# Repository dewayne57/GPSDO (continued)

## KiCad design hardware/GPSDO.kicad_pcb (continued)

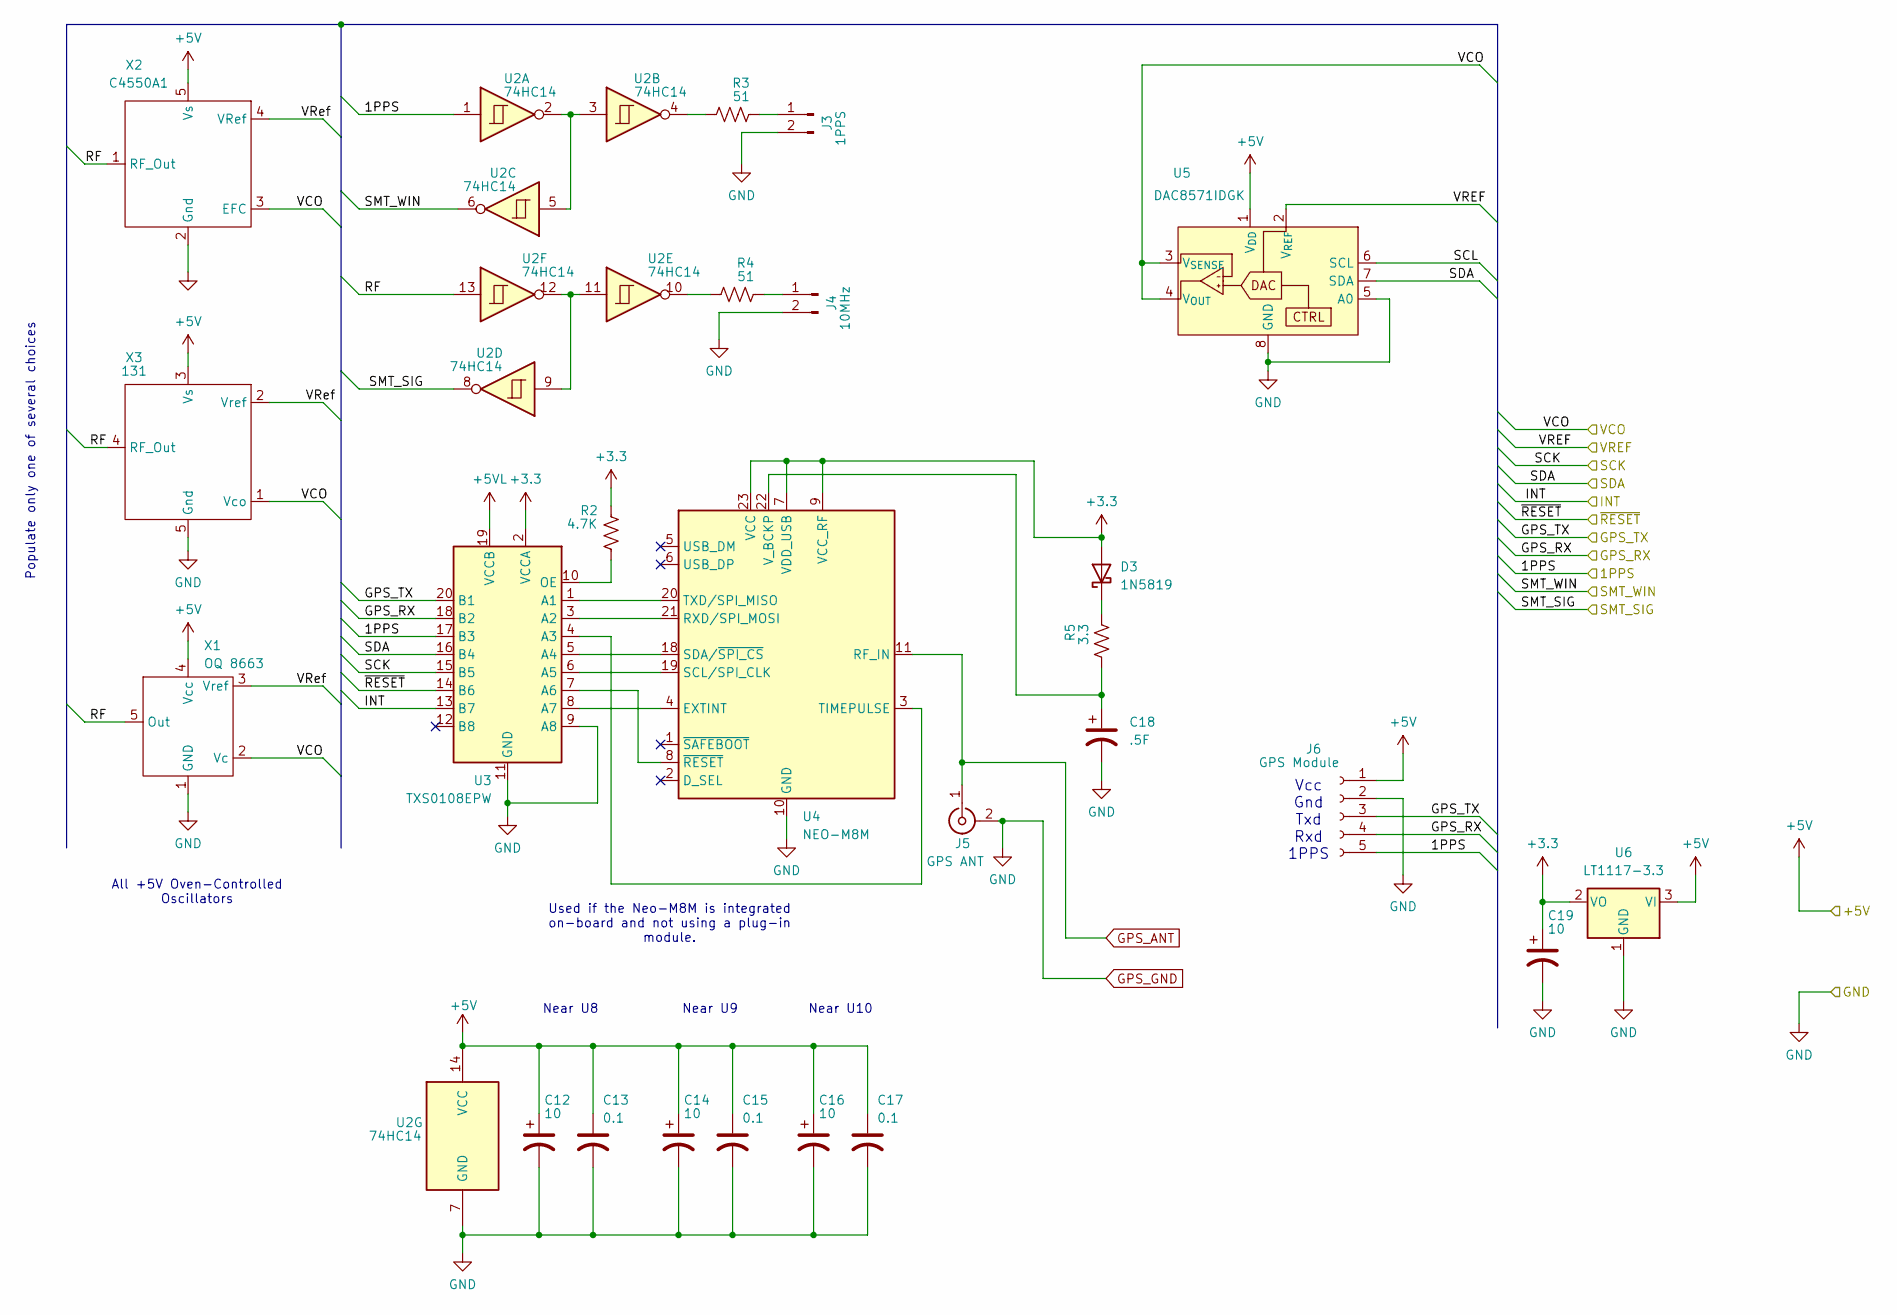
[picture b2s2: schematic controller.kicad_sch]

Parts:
C12, C14, C16, C19: 10; CP_Elec_5x5.4
C13, C15, C17: 0.1; C_0805_2012Metric_Pad1.18x1.45mm_HandSolder
C18: .5F
D3: 1N5819; D_DO-41_SOD81_P10.16mm_Horizontal
J3: 1PPS; PinHeader_1x02_P2.54mm_Vertical
J4: 10MHz; PinHeader_1x02_P2.54mm_Vertical
J5: GPS ANT; SMA_Amphenol_901-144_Vertical
J6: GPS Module; PinHeader_1x05_P2.54mm_Vertical
R2: 4.7K; R_0805_2012Metric_Pad1.20x1.40mm_HandSolder
R3, R4: 51; R_0805_2012Metric_Pad1.20x1.40mm_HandSolder
R5: 3.3; R_0805_2012Metric_Pad1.20x1.40mm_HandSolder
U2: 74HC14; SO-14_5.3x10.2mm_P1.27mm
U3: TXS0108EPW; TSSOP-20_4.4x6.5mm_P0.65mm
U4: NEO-M8M; ublox_NEO
U5: DAC8571IDGK; MSOP-8_3x3mm_P0.65mm
U6: LT1117-3.3; SOT-223
X1: OQ 8663; OQ8663
X2: C4550A1; C4550-OCXO
X3: 131; ISOTEMP 131

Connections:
+3.3: C19.1, D3.2 (A), R2.1, U3.2 (VCCA), U4.7 (VDD_USB), U4.9 (VCC_RF), U4.23 (VCC), U6.2 (VO); also elsewhere on the board
+5V: C12.1, C13.1, C14.1, C15.1, C16.1, C17.1, J6.1, U2.14 (VCC), U5.1 (V_{DD}), U6.3 (VI), X1.4 (Vcc), X2.5 (Vs), X3.3 (Vs); also elsewhere on the board
+5VL: U3.19 (VCCB)
/Loop Controller/1PPS: J6.5, U2.1, U3.17 (B3); also elsewhere on the board
/Loop Controller/GPS_RX: J6.4, U3.18 (B2); also elsewhere on the board
/Loop Controller/GPS_TX: J6.3, U3.20 (B1); also elsewhere on the board
/Loop Controller/INT: U3.13 (B7); also elsewhere on the board
/Loop Controller/RF: U2.13, X1.5 (Out), X2.1 (RF_Out), X3.4 (RF_Out)
/Loop Controller/SCK: U3.15 (B5)
/Loop Controller/SCL: U5.6 (SCL)
/Loop Controller/SDA: U3.16 (B4), U5.7 (SDA); also elsewhere on the board
/Loop Controller/SMT_SIG: U2.8; also elsewhere on the board
/Loop Controller/SMT_WIN: U2.6; also elsewhere on the board
/Loop Controller/VCO: U5.3 (V_{SENSE}), U5.4 (V_{OUT}), X1.2 (Vc), X2.3 (EFC), X3.1 (Vco); also elsewhere on the board
/Loop Controller/VREF: U5.2 (V_{REF}); also elsewhere on the board
/Loop Controller/VRef: X1.3 (Vref), X2.4 (VRef), X3.2 (Vref)
/Loop Controller/~RESET: U3.14 (B6); also elsewhere on the board
Earth_Protective: C12.2, C13.2, C14.2, C15.2, C16.2, C17.2, C18.2, C19.2, J3.2, J4.2, J5.2 (Ext), J6.2, U2.7 (GND), U3.9 (A8), U3.11 (GND), U4.10 (GND), U4.12 (GND), U4.13 (GND), U4.24 (GND), U5.5 (A0), U5.8 (GND), U6.1 (GND), X1.1 (GND), X2.2 (Gnd), X3.5 (Gnd); also elsewhere on the board
GPS_ANT: J5.1 (In), U4.11 (RF_IN)
unnamed: D3.1 (K), R5.2
unnamed: J3.1, R3.2
unnamed: J4.1, R4.2
unnamed: R3.1, U2.4
unnamed: R4.1, U2.10
unnamed: U2.2, U2.3, U2.5
unnamed: U2.9, U2.11, U2.12
unnamed: U3.1 (A1), U4.20 (TXD/SPI_MISO)
unnamed: U3.3 (A2), U4.21 (RXD/SPI_MOSI)
unnamed: U3.4 (A3), U4.3 (TIMEPULSE)
unnamed: U3.5 (A4), U4.18 (SDA/~SPI_CS)
unnamed: U3.6 (A5), U4.19 (SCL/SPI_CLK)
unnamed: U3.7 (A6), U4.8 (~RESET)
unnamed: U3.8 (A7), U4.4 (EXTINT)
unnamed: R2.2, U3.10 (OE)
unnamed: C18.1, R5.1, U4.22 (V_BCKP)

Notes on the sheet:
Near U8
Vcc Gnd Txd Rxd 1PPS
Near U10
Used if the Neo-M8M is integrated on-board and not using a plug-in module.
Populate only one of several choices
Near U9
All +5V Oven-Controlled Oscillators

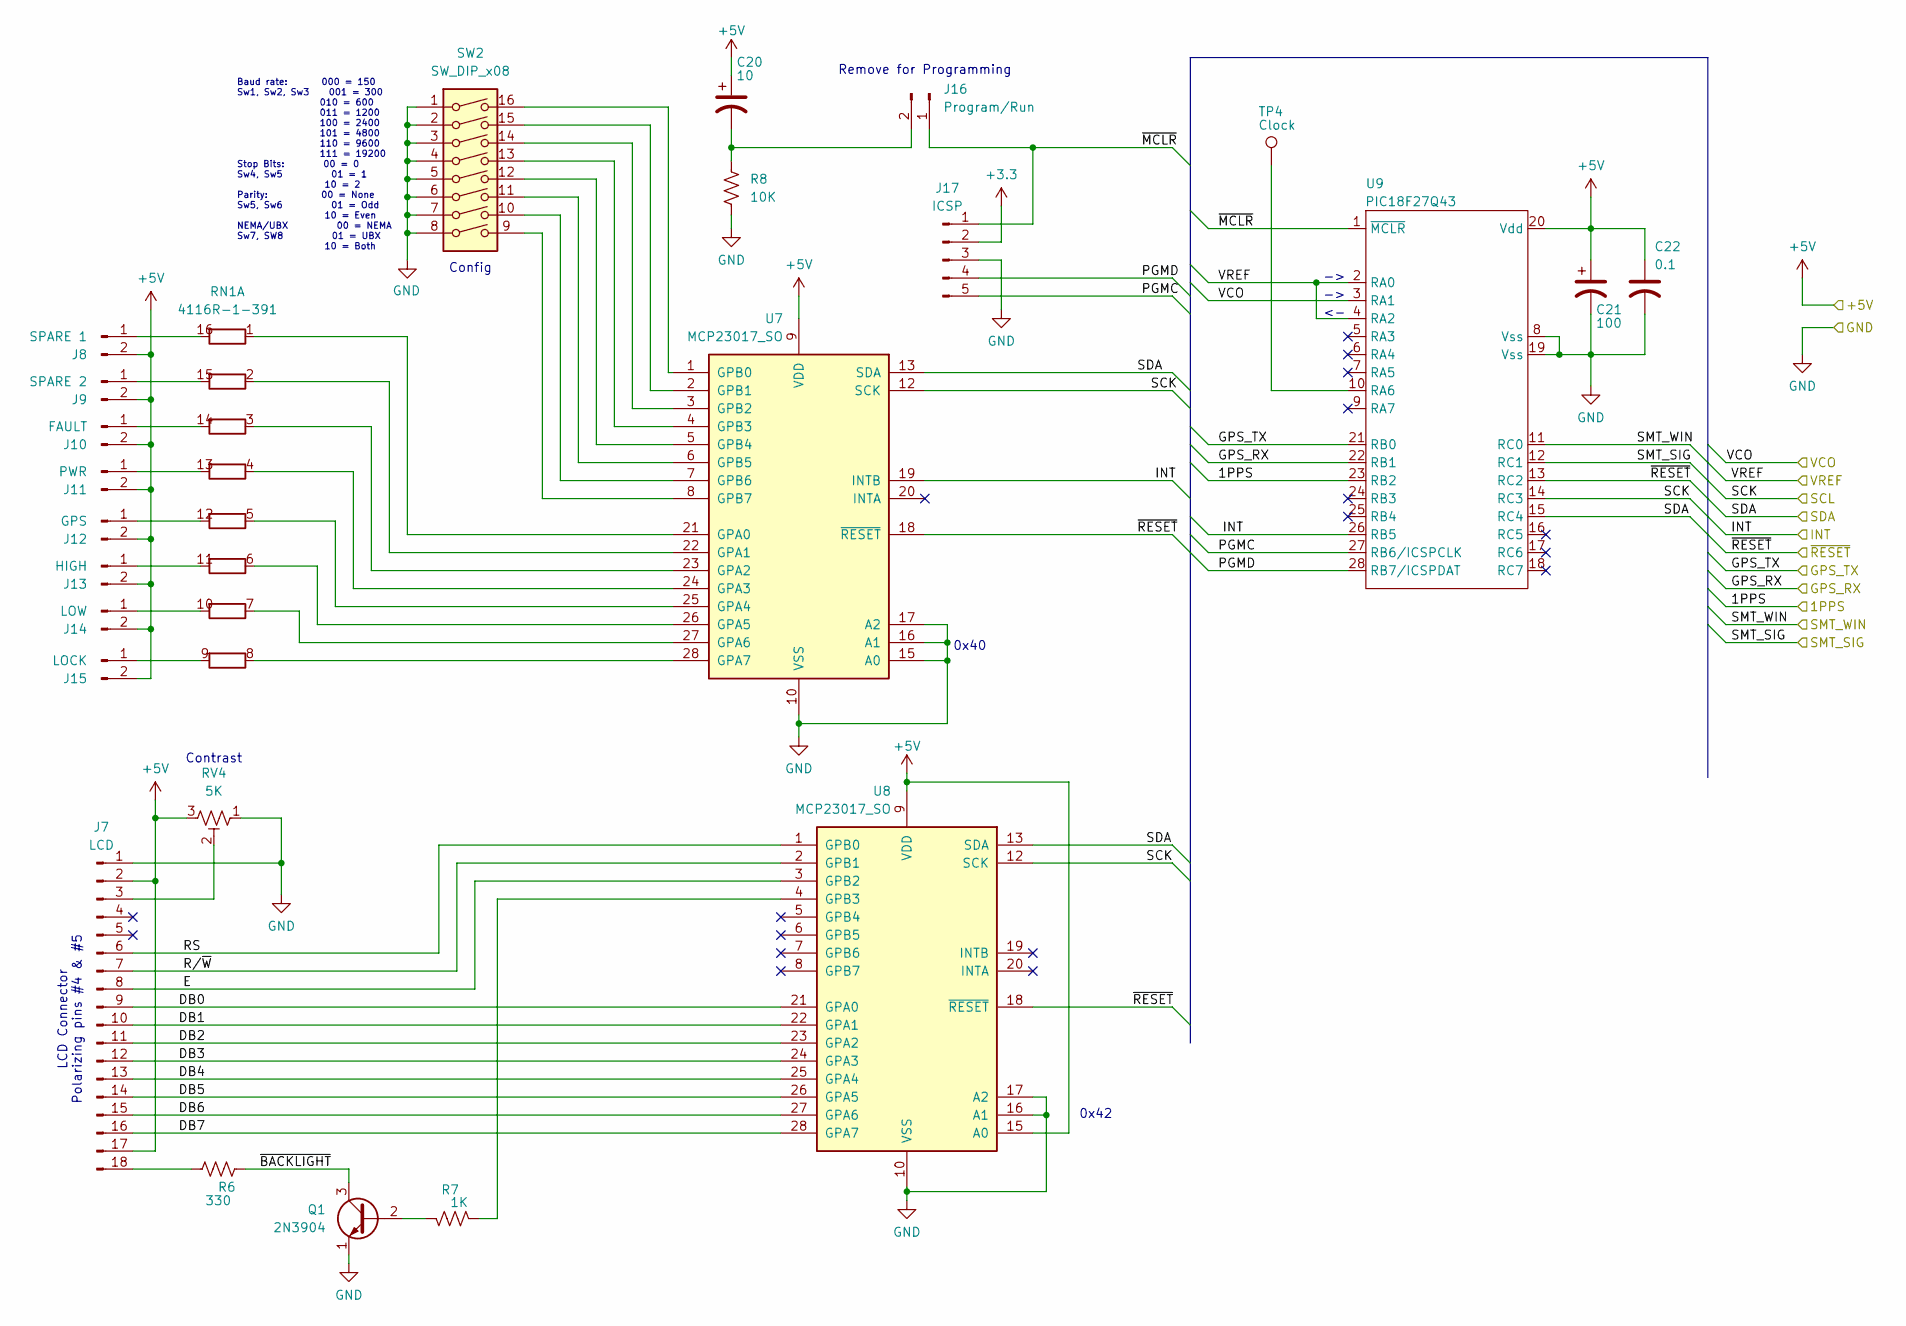
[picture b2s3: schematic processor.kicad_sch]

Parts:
C20: 10; CP_Elec_5x5.4
C21: 100; CP_Elec_6.3x7.7
C22: 0.1; C_0805_2012Metric_Pad1.18x1.45mm_HandSolder
J7: LCD; PinHeader_1x18_P2.54mm_Vertical
J8: SPARE 1; PinHeader_1x02_P2.54mm_Vertical
J9: SPARE 2; PinHeader_1x02_P2.54mm_Vertical
J10: FAULT; PinHeader_1x02_P2.54mm_Vertical
J11: PWR; PinHeader_1x02_P2.54mm_Vertical
J12: GPS; PinHeader_1x02_P2.54mm_Vertical
J13: HIGH; PinHeader_1x02_P2.54mm_Vertical
J14: LOW; PinHeader_1x02_P2.54mm_Vertical
J15: LOCK; PinHeader_1x02_P2.54mm_Vertical
J16: Program/Run; PinHeader_1x02_P2.54mm_Vertical
J17: ICSP; PinHeader_1x05_P2.54mm_Vertical
Q1: 2N3904; TO-92_Inline
R6: 330; R_0805_2012Metric_Pad1.20x1.40mm_HandSolder
R7: 1K; R_0805_2012Metric_Pad1.20x1.40mm_HandSolder
R8: 10K; R_0805_2012Metric_Pad1.20x1.40mm_HandSolder
RN1: 4116R-1-391; DIP-16_W7.62mm_LongPads
RV4: 5K; Potentiometer_Bourns_3296W_Vertical
SW2: SW_DIP_x08; DIP-16_W7.62mm_LongPads
TP4: Clock
U7, U8: MCP23017_SO; SOIC-28W_7.5x17.9mm_P1.27mm
U9: PIC18F27Q43; SOIC-28W_7.5x17.9mm_P1.27mm

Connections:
+3.3: J17.2; also elsewhere on the board
+5V: C20.1, C21.1, C22.1, J7.2, J7.17, J8.2, J9.2, J10.2, J11.2, J12.2, J13.2, J14.2, J15.2, RV4.3, U7.9 (VDD), U8.9 (VDD), U8.15 (A0), U9.20 (Vdd); also elsewhere on the board
/Loop Controller/1PPS: U9.23 (RB2); also elsewhere on the board
/Loop Controller/GPS_RX: U9.22 (RB1); also elsewhere on the board
/Loop Controller/GPS_TX: U9.21 (RB0); also elsewhere on the board
/Loop Controller/INT: U7.19 (INTB), U9.26 (RB5); also elsewhere on the board
/Loop Controller/SDA: U7.13 (SDA), U8.13 (SDA), U9.15 (RC4); also elsewhere on the board
/Loop Controller/SMT_SIG: U9.12 (RC1); also elsewhere on the board
/Loop Controller/SMT_WIN: U9.11 (RC0); also elsewhere on the board
/Loop Controller/VCO: U9.3 (RA1); also elsewhere on the board
/Loop Controller/VREF: U9.2 (RA0), U9.4 (RA2); also elsewhere on the board
/Loop Controller/~RESET: U7.18 (~RESET), U8.18 (~RESET), U9.13 (RC2); also elsewhere on the board
/Processor/DB0: J7.9, U8.21 (GPA0)
/Processor/DB1: J7.10, U8.22 (GPA1)
/Processor/DB2: J7.11, U8.23 (GPA2)
/Processor/DB3: J7.12, U8.24 (GPA3)
/Processor/DB4: J7.13, U8.25 (GPA4)
/Processor/DB5: J7.14, U8.26 (GPA5)
/Processor/DB6: J7.15, U8.27 (GPA6)
/Processor/DB7: J7.16, U8.28 (GPA7)
/Processor/E: J7.8, U8.3 (GPB2)
/Processor/PGMC: J17.5, U9.27 (RB6/ICSPCLK)
/Processor/PGMD: J17.4, U9.28 (RB7/ICSPDAT)
/Processor/RS: J7.6, U8.1 (GPB0)
/Processor/R/~W: J7.7, U8.2 (GPB1)
/Processor/SCK: U7.12 (SCK), U8.12 (SCK), U9.14 (RC3)
/Processor/~BACKLIGHT: Q1.3 (C), R6.2
/Processor/~MCLR: J16.1, J17.1, U9.1 (~MCLR)
Earth_Protective: C21.2, C22.2, J7.1, J17.3, Q1.1 (E), R8.2, RV4.1, SW2.1, SW2.2, SW2.3, SW2.4, SW2.5, SW2.6, SW2.7, SW2.8, U7.10 (VSS), U7.15 (A0), U7.16 (A1), U7.17 (A2), U8.10 (VSS), U8.16 (A1), U8.17 (A2), U9.8 (Vss), U9.19 (Vss); also elsewhere on the board
unnamed: J7.3, RV4.2
unnamed: J7.18, R6.1
unnamed: J8.1, RN1.16 (R1.2)
unnamed: J9.1, RN1.15 (R2.2)
unnamed: J10.1, RN1.14 (R3.2)
unnamed: J11.1, RN1.13 (R4.2)
unnamed: J12.1, RN1.12 (R5.2)
unnamed: J13.1, RN1.11 (R6.2)
unnamed: J14.1, RN1.10 (R7.2)
unnamed: J15.1, RN1.9 (R8.2)
unnamed: C20.2, J16.2, R8.1
unnamed: Q1.2 (B), R7.2
unnamed: RN1.1 (R1.1), U7.21 (GPA0)
unnamed: RN1.2 (R2.1), U7.22 (GPA1)
unnamed: RN1.3 (R3.1), U7.23 (GPA2)
unnamed: RN1.4 (R4.1), U7.24 (GPA3)
unnamed: RN1.5 (R5.1), U7.25 (GPA4)
unnamed: RN1.6 (R6.1), U7.26 (GPA5)
unnamed: RN1.7 (R7.1), U7.27 (GPA6)
unnamed: RN1.8 (R8.1), U7.28 (GPA7)
unnamed: SW2.16, U7.1 (GPB0)
unnamed: SW2.15, U7.2 (GPB1)
unnamed: SW2.14, U7.3 (GPB2)
unnamed: SW2.13, U7.4 (GPB3)
unnamed: SW2.12, U7.5 (GPB4)
unnamed: SW2.11, U7.6 (GPB5)
unnamed: SW2.10, U7.7 (GPB6)
unnamed: SW2.9, U7.8 (GPB7)
unnamed: R7.1, U8.4 (GPB3)
unnamed: TP4.1, U9.10 (RA6)

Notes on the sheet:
0x40
Contrast
Remove for Programming
0x42
LCD Connector Polarizing pins #4 & #5
Baud rate: 000 = 150 Sw1, Sw2, Sw3 001 = 300 010 = 600 011 = 1200 100 = 2400 101 = 4800 110 = 9600 111 = 19200 Stop Bits: 00 = 0 Sw4, Sw5 01 = 1 10 = 2 Parity: 00 = None Sw5, Sw6 01 = Odd 10 = Even NEMA/UBX 00 = NEMA Sw7, SW8 01 = UBX 10 = Both
Config

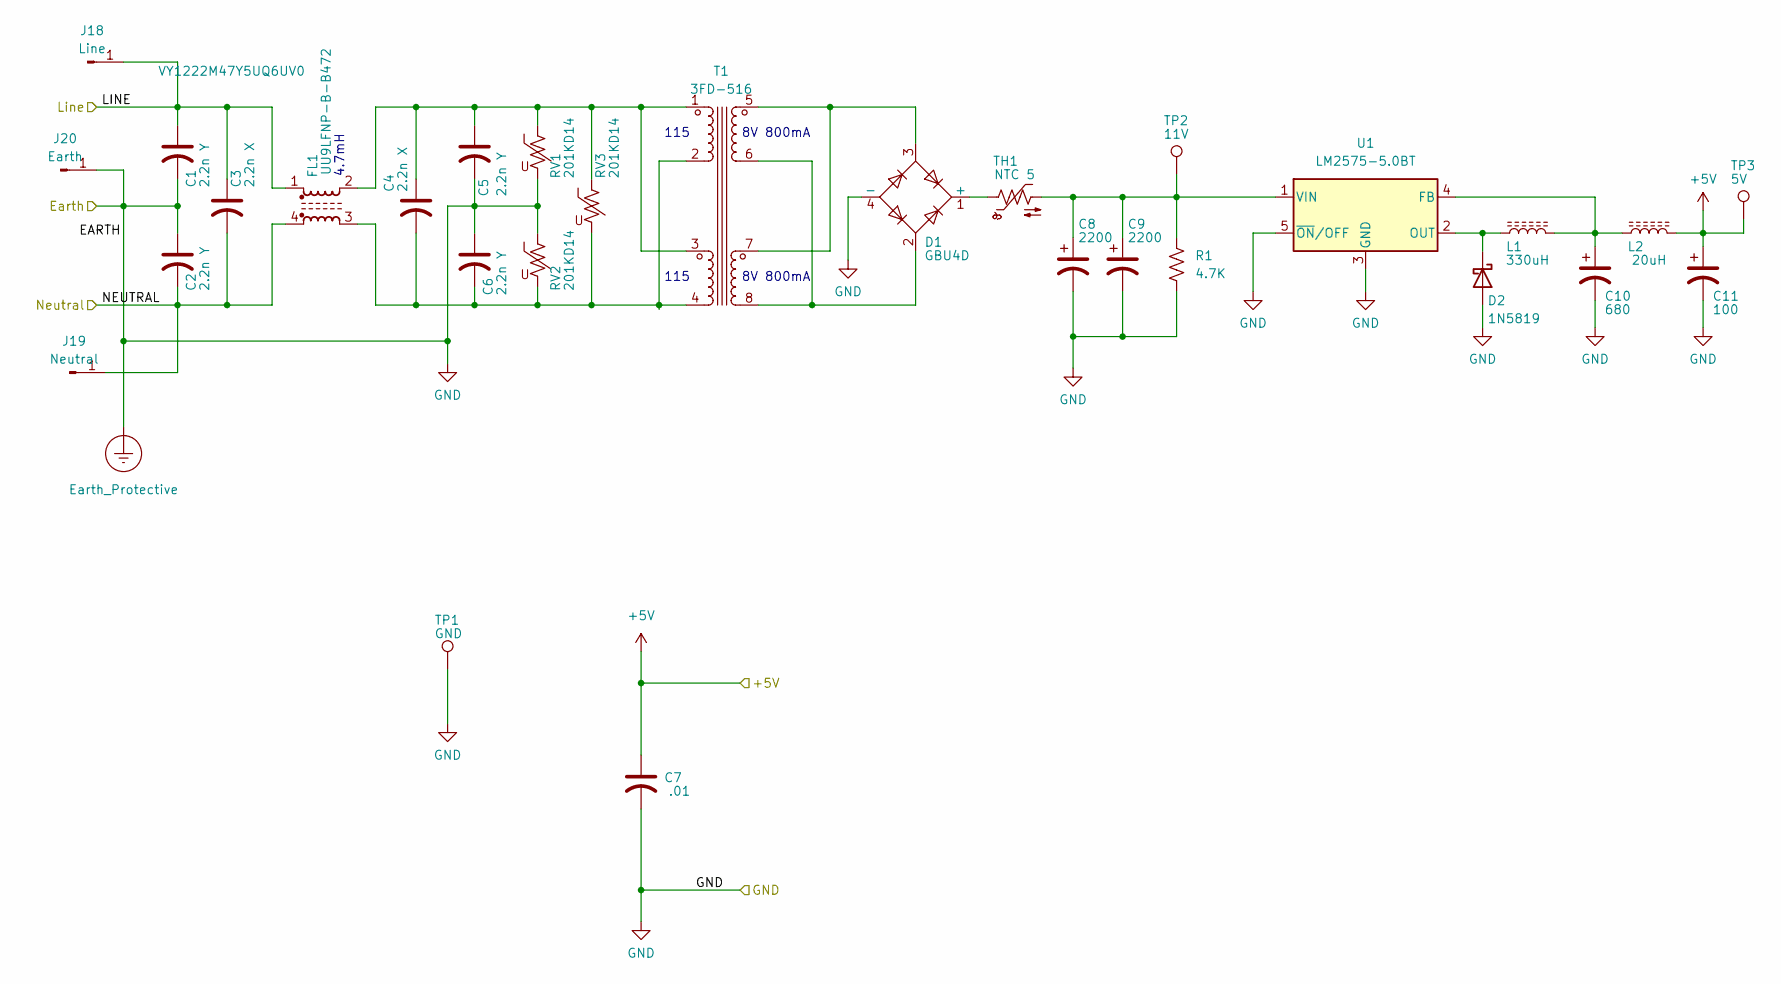
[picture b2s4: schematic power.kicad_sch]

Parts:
C1, C2, C5, C6: 2.2n Y; C_Disc_D12.5mm_W5.0mm_P10.00mm
C3, C4: 2.2n X; C_Disc_D12.5mm_W5.0mm_P10.00mm
C7: .01; C_0805_2012Metric_Pad1.18x1.45mm_HandSolder
C8, C9: 2200; CP_Radial_D18.0mm_P7.50mm
C10: 680; CP_Elec_10x10
C11: 100; CP_Elec_6.3x7.7
D1: GBU4D; Diode_Bridge_Vishay_GBU
D2: 1N5819; D_SOD-123
FL1: UU9LFNP-B-B472; L_CommonMode_PulseElectronics_PH9455xxx6NL_2
J18: Line; SolderWire-1sqmm_1x01_D1.4mm_OD2.7mm
J19: Neutral; SolderWire-1sqmm_1x01_D1.4mm_OD2.7mm
J20: Earth; SolderWire-1sqmm_1x01_D1.4mm_OD2.7mm
L1: 330uH; L_12x12mm_H8mm
L2: 20uH; L_TDK_VLF10040
R1: 4.7K; R_0805_2012Metric_Pad1.20x1.40mm_HandSolder
RV1, RV2, RV3: 201KD14; RV_Rect_V25S440P_L26.5mm_W8.2mm_P12.7mm
T1: 3FD-516; 3FD
TH1: NTC 5; C_Disc_D8.0mm_W5.0mm_P5.00mm
TP1: GND; TestPoint_Bridge_Pitch2.54mm_Drill0.7mm
TP2: 11V; TestPoint_Bridge_Pitch2.54mm_Drill0.7mm
TP3: 5V; TestPoint_Bridge_Pitch2.54mm_Drill0.7mm
U1: LM2575-5.0BT; TO-220-5_P3.4x3.7mm_StaggerOdd_Lead3.8mm_Vertical

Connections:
+5V: C7.1, C11.1, L2.2, TP3.1; also elsewhere on the board
/Power Supply/LINE: C1.1, C3.1, FL1.1, J18.1
/Power Supply/NEUTRAL: C2.2, C3.2, FL1.4, J19.1
Earth_Protective: C1.2, C2.1, C5.2, C6.1, C7.2, C8.2, C9.2, C10.2, C11.2, D1.4 (-), D2.2 (A), J20.1, R1.2, RV1.2, RV2.1, TP1.1, U1.3 (GND), U1.5 (~ON/OFF); also elsewhere on the board
unnamed: C4.1, C5.1, FL1.2, RV1.1, RV3.1, T1.1, T1.3
unnamed: C4.2, C6.2, FL1.3, RV2.2, RV3.2, T1.2, T1.4
unnamed: D1.1 (+), TH1.1
unnamed: D1.2, T1.6, T1.8
unnamed: D1.3, T1.5, T1.7
unnamed: D2.1 (K), L1.1, U1.2 (OUT)
unnamed: C10.1, L1.2, L2.1, U1.4 (FB)
unnamed: C8.1, C9.1, R1.1, TH1.2, TP2.1, U1.1 (VIN)

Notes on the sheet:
115
8V 800mA
4.7mH

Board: 2 copper layers, 77 parts (0 on the bottom side), 87 nets, no tracks yet.

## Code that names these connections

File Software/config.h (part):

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#pragma config CSWEN = OFF              // No clock switching allowed
#pragma config FCMEN = OFF              // Fail-safe clock monitor is disabled
#pragma config PR1WAY = 0               // PRLOCKED Set/Cleared repeatedly
#pragma config CLKOUTEN = 0             // Clock out is enabled on RA6
#pragma config BOREN = 3                // Brown-out reset is enabled
#pragma config LPBOREN = OFF            // Low power brown-out reset is disabled
#pragma config IVT1WAY = 0              // IVTLOCK Set/cleared repeatedly
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/****************************************************************************/

// Port A
#define VREF_FB 1                               // RA0: VREF feedback pin
#define INT_REF 2                               // RA1: Internal reference output pin
#define CLOCK_OUT 64                            // RA6: Clock output pin

// Port B
#define EXT_TX 1                                // RB0: External TX output
#define EXT_RX 2                                // RB1: External RX input
#define USB_TX 4                                // RB2: USB interface transmit pin
#define USB_RX 8                                // RB3: USB interface receive pin
#define GPS_TX 16                               // RB4: GPS Transmit pin
#define GPS_RX 32                               // RB5: GPS Receive pin
#define PROGRAM_N 64                            // RB6: Program mode select (active LOW)

// Port C
#define PPS 1                                   // RC0: 1PPS signal from GPS module
#define RF 2                                    // RC1: RF From OCXO
#define RESET_N 4                               // RC2: Active low reset for io expander
#define SCL 8                                   // RC3: I2C Clock
#define SDA 16                                  // RC4: I2C Data
#define PHASE_A 32                              // RC5: Phase A input from encoder
#define PHASE_B 64                              // RC6: Phase B input from encoder
#define ENTER_N 128                             // RC7: Active low enter button

/****************************************************************************/
/*                                                                          */
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/****************************************************************************/
typedef union {
    struct {
        unsigned char LCD_RS : 1;               // LCD Register Select pin
        unsigned char LCD_RW : 1;               // LCD Read/Write pin
        unsigned char LCD_E : 1;                // LCD Enable pin
        unsigned char LCD_BL : 1;               // LCD Backlight control pin
        unsigned char NYBBLE: 4;                // LCD data nybble (upper 4 bits)
    };
    unsigned char all;
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
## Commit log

2025-10-26 Added Schematic Files
2025-10-26 Expanded readme
2025-10-26 Adding more description
2025-10-28 Revised hardware design
2025-10-28 Revised readme.md
2025-12-18 Initial creation
2025-12-18 added GPS receive and parse; configuration options; menu options; converted from PID to PI control.
2025-12-18 remove all tabs and refomat
2025-12-19 updates to documentation
2025-12-20 Working on LCD routines
2025-12-21 (lib_symbols (symbol "power:GND" (power) (pin_numbers (hide yes) ) (pin_names (offset 0) (hide yes) ) (exclude_from_sim no) (in_bom yes) (on_board yes) (property "Reference" "#PWR" (at 0 -6.35 0) (ef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
2025-12-22 menu updtes
2025-12-22 updated schematics
2025-12-23 LCD now working
2025-12-24 debugging
2025-12-25 fixed review issues
2025-12-27 processing gps sentences
2025-12-27 processing gps
2025-12-27 rewrite gps buffering
2025-12-28 cleanup
2025-12-28 updated gps serial
2025-12-28 serial
2025-12-29 general cleanup
2026-01-01 changed uarts and lcd pins
2026-01-01 deleted files should be in ignore
2026-01-04 Added Faults
2026-01-04 changes to lcd
2026-01-05 removed dead code
2026-01-23 Updated PCB
2026-01-25 Corrected IIC code
2026-01-26 Updated Schematic; Move to SMD
2026-01-30 Updated PCB; ran DRC; fixing errors
2026-01-30 finished pcb drc edits
